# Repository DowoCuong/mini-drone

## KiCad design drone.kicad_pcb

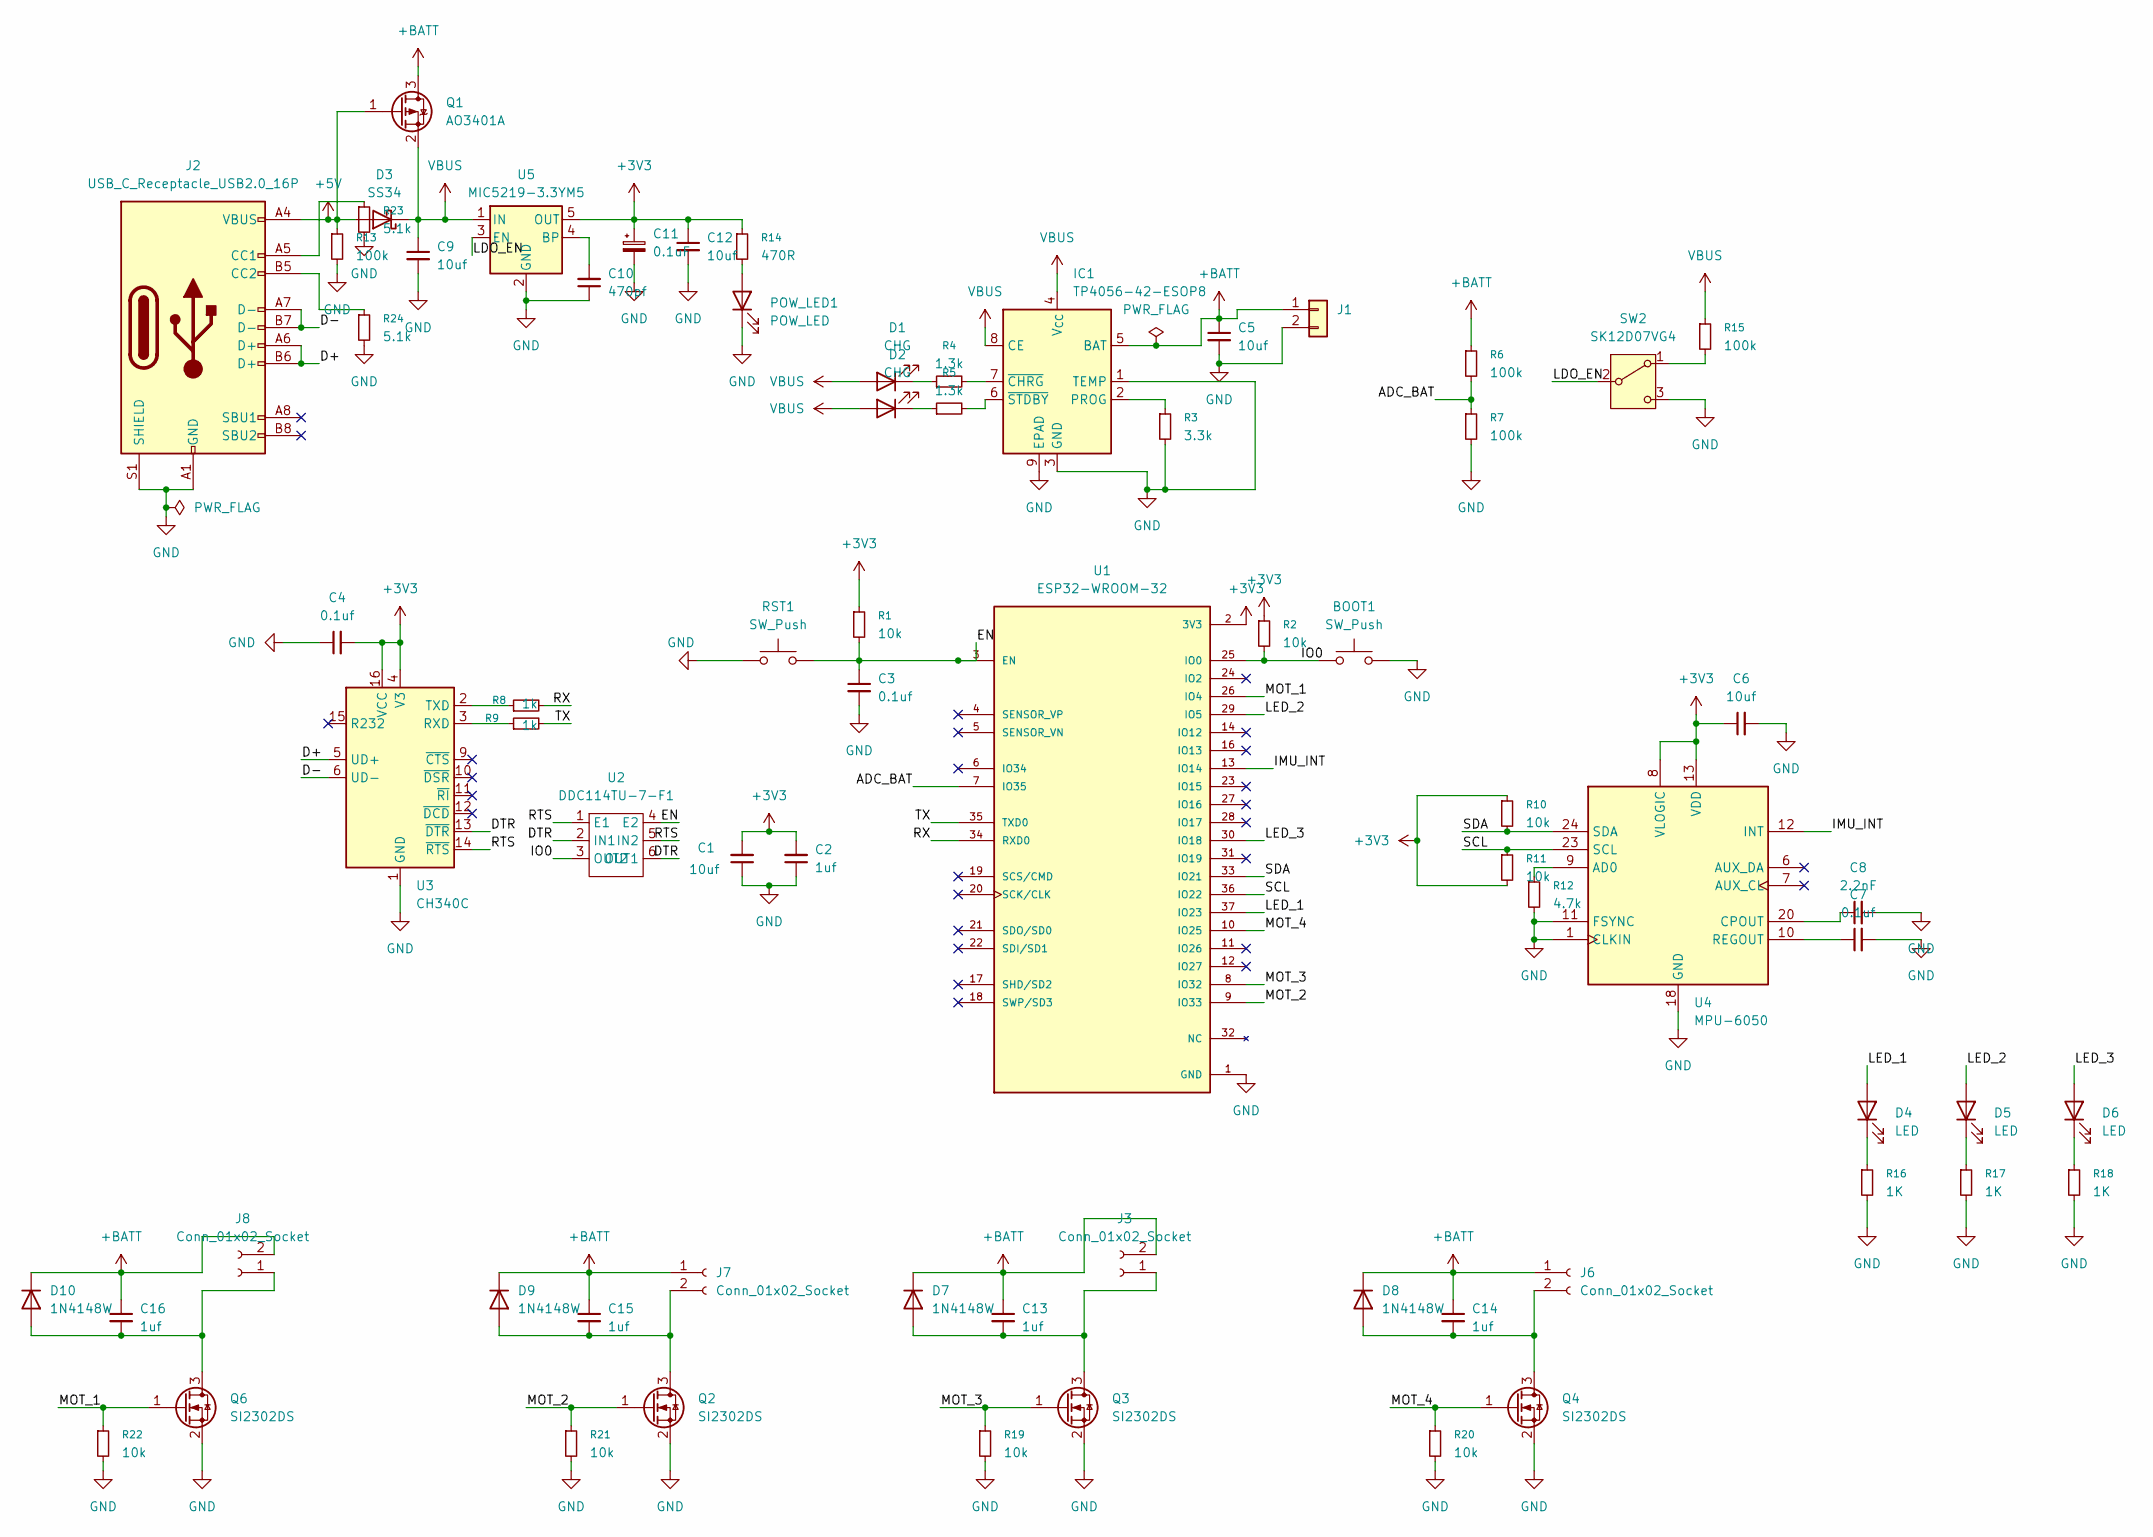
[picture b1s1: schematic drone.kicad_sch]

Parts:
BOOT1: SW_Push; SW_SPST_TL3342
C1, C5, C6, C9, C12: 10uf; C_0603_1608Metric
C2, C13, C14, C15, C16: 1uf; C_0603_1608Metric
C3, C4, C7: 0.1uf; C_0603_1608Metric
C8: 2.2nF; C_0603_1608Metric
C10: 470pf; C_0603_1608Metric
C11: 0.1uF; C_0805_2012Metric
D1, D2: CHG; LED_0603_1608Metric
D3: SS34; D_SMA
D4, D5, D6: LED; LED_0603_1608Metric
D7, D8, D9, D10: 1N4148W; D_SOD-123F
IC1: TP4056-42-ESOP8; SOIC-8-1EP_3.9x4.9mm_P1.27mm_EP2.41x3.3mm_ThermalVias
J1: SolderPads_2x_0.75sqmm_P4.8mm
J2: USB_C_Receptacle_USB2.0_16P; USB_C_HRO_TYPE-C-31-M-12_Drone
J3, J6, J7, J8: Conn_01x02_Socket; SolderPads_2x_0.75sqmm_P4.8mm
POW_LED1: POW_LED; LED_0603_1608Metric
Q1: AO3401A; SOT-23
Q2, Q3, Q4, Q6: SI2302DS; SOT-23
R1, R2, R10, R11, R19, R20, R21, R22: 10k; R_0603_1608Metric
R3: 3.3k; R_0603_1608Metric
R4, R5: 1.3k; R_0603_1608Metric
R6, R7, R13, R15: 100k; R_0603_1608Metric
R8, R9: 1k; R_0603_1608Metric
R12: 4.7k; R_0603_1608Metric
R14: 470R; R_0603_1608Metric
R16, R17, R18: 1K; R_0603_1608Metric
R23, R24: 5.1k; R_0603_1608Metric
RST1: SW_Push; SW_SPST_TL3342
SW2: SK12D07VG4; SW_SPDT_SK12D07VG4_THT
U1: ESP32-WROOM-32; MODULE_ESP32-WROOM-32_Drone_AntennaKeepout; PARTREV 2.9
U2: DDC114TU-7-F1; SOT-363_SC-70-6
U3: CH340C; SOIC-16_3.9x9.9mm_P1.27mm
U4: MPU-6050; InvenSense_QFN-24_4x4mm_P0.5mm
U5: MIC5219-3.3YM5; SOT-23-5

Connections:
+3V3: C1.2, C2.2, C4.2, C6.1, C11.1, C12.1, R1.1, R2.1, R10.1, R11.2, R14.1, U1.2 (3V3), U3.4 (V3), U3.16 (VCC), U4.8 (VLOGIC), U4.13 (VDD), U5.5 (OUT)
+5V: D3.2 (A), J2.A4 (VBUS), J2.A9 (VBUS), J2.B4 (VBUS), J2.B9 (VBUS), Q1.1 (G), R13.1
+BATT: C5.1, C13.1, C14.1, C15.1, C16.1, D7.1 (K), D8.1 (K), D9.1 (K), D10.1 (K), IC1.5 (BAT), J1.1, J3.2, J6.1, J7.1, J8.2, Q1.3 (D), R6.1
/ADC_BAT: R6.2, R7.1, U1.7 (IO35)
/D+: J2.A6 (D+), J2.B6 (D+), U3.5 (UD+)
/D-: J2.A7 (D-), J2.B7 (D-), U3.6 (UD-)
/DTR: U2.2 (IN1), U2.6 (OUT1), U3.13 (~DTR)
/EN: C3.1, R1.2, RST1.2, U1.3 (EN), U2.4 (E2)
/IMU_INT: U1.13 (IO14), U4.12 (INT)
/IO0: BOOT1.1, R2.2, U1.25 (IO0), U2.3 (OUT2)
/LDO_EN: SW2.2 (B), U5.3 (EN)
/LED_1: D4.2 (A), U1.37 (IO23)
/LED_2: D5.2 (A), U1.29 (IO5)
/LED_3: D6.2 (A), U1.30 (IO18)
/MOT_1: Q6.1 (G), R22.1, U1.26 (IO4)
/MOT_2: Q2.1 (G), R21.1, U1.9 (IO33)
/MOT_3: Q3.1 (G), R19.1, U1.8 (IO32)
/MOT_4: Q4.1 (G), R20.1, U1.10 (IO25)
/RTS: U2.1 (E1), U2.5 (IN2), U3.14 (~RTS)
/RX: R8.2, U1.34 (RXD0)
/SCL: R11.1, U1.36 (IO22), U4.23 (SCL)
/SDA: R10.2, U1.33 (IO21), U4.24 (SDA)
/TX: R9.2, U1.35 (TXD0)
GND: BOOT1.2, C1.1, C2.1, C3.2, C4.1, C5.2, C6.2, C7.2, C8.2, C9.2, C10.1, C11.2, C12.2, IC1.1 (TEMP), IC1.3 (GND), IC1.9 (EPAD), J1.2, J2.A1 (GND), J2.A12 (GND), J2.B1 (GND), J2.B12 (GND), J2.S1 (SHIELD), POW_LED1.1 (K), Q2.2 (S), Q3.2 (S), Q4.2 (S), Q6.2 (S), R3.2, R7.2, R12.2, R13.2, R16.2, R17.2, R18.2, R19.2, R20.2, R21.2, R22.2, R23.2, R24.2, RST1.1, SW2.3 (C), U1.1 (GND), U1.15 (GND), U1.38 (GND), U1.39_1 (GND), U1.39_2 (GND), U1.39_3 (GND), U1.39_4 (GND), U1.39_5 (GND), U1.39_6 (GND), U1.39_7 (GND), U1.39_8 (GND), U1.39_9 (GND), U1.39_10 (GND), U1.39_11 (GND), U1.39_12 (GND), U1.39_13 (GND), U1.39_14 (GND), U1.39_15 (GND), U1.39_16 (GND), U1.39_17 (GND), U1.39_18 (GND), U1.39_19 (GND), U1.39_20 (GND), U1.39_21 (GND), U3.1 (GND), U4.1 (CLKIN), U4.11 (FSYNC), U4.18 (GND), U5.2 (GND)
unnamed: D1.1 (K), R4.1
unnamed: D2.1 (K), R5.1
unnamed: D4.1 (K), R16.1
unnamed: D5.1 (K), R17.1
unnamed: D6.1 (K), R18.1
unnamed: C13.2, D7.2 (A), J3.1, Q3.3 (D)
unnamed: C14.2, D8.2 (A), J6.2, Q4.3 (D)
unnamed: C15.2, D9.2 (A), J7.2, Q2.3 (D)
unnamed: C16.2, D10.2 (A), J8.1, Q6.3 (D)
unnamed: IC1.2 (PROG), R3.1
unnamed: IC1.7 (~CHRG), R4.2
unnamed: IC1.6 (~STDBY), R5.2
unnamed: J2.A5 (CC1), R23.1
unnamed: J2.B5 (CC2), R24.1
unnamed: POW_LED1.2 (A), R14.2
unnamed: R15.2, SW2.1 (A)
unnamed: R9.1, U3.3 (RXD)
unnamed: R8.1, U3.2 (TXD)
unnamed: R12.1, U4.9 (AD0)
unnamed: C8.1, U4.20 (CPOUT)
unnamed: C7.1, U4.10 (REGOUT)
unnamed: C10.2, U5.4 (BP)
VBUS: C9.1, D1.2 (A), D2.2 (A), D3.1 (K), IC1.4 (V_{CC}), IC1.8 (CE), Q1.2 (S), R15.1, U5.1 (IN)

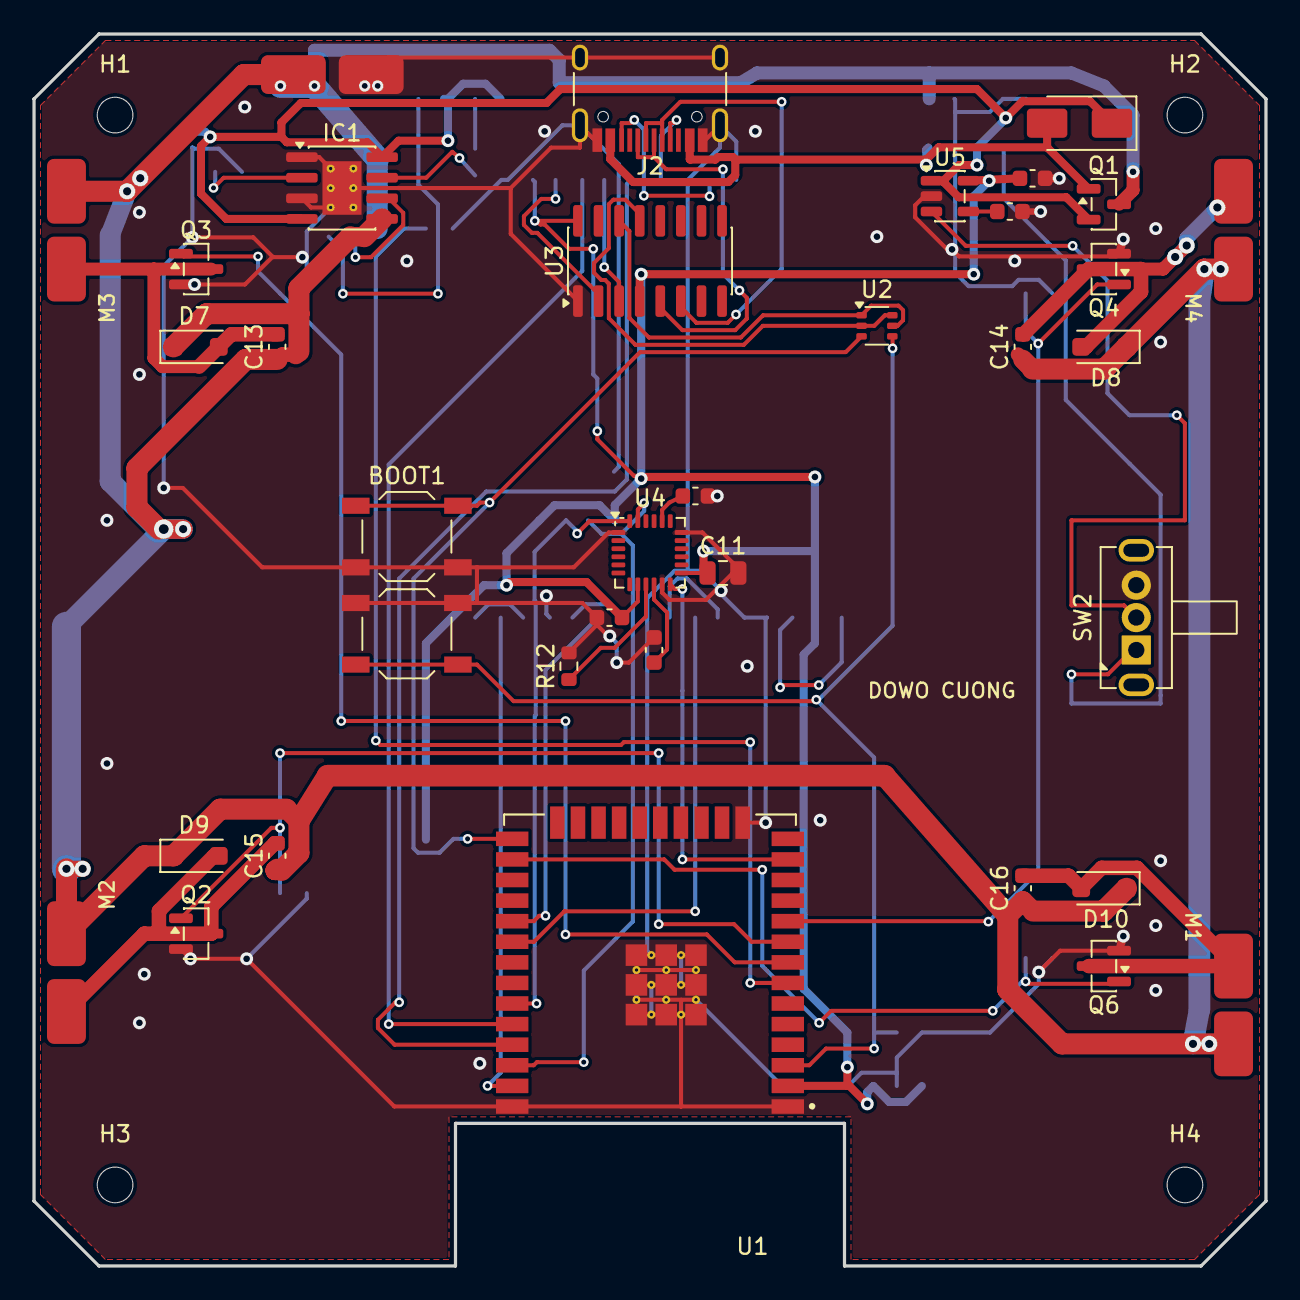
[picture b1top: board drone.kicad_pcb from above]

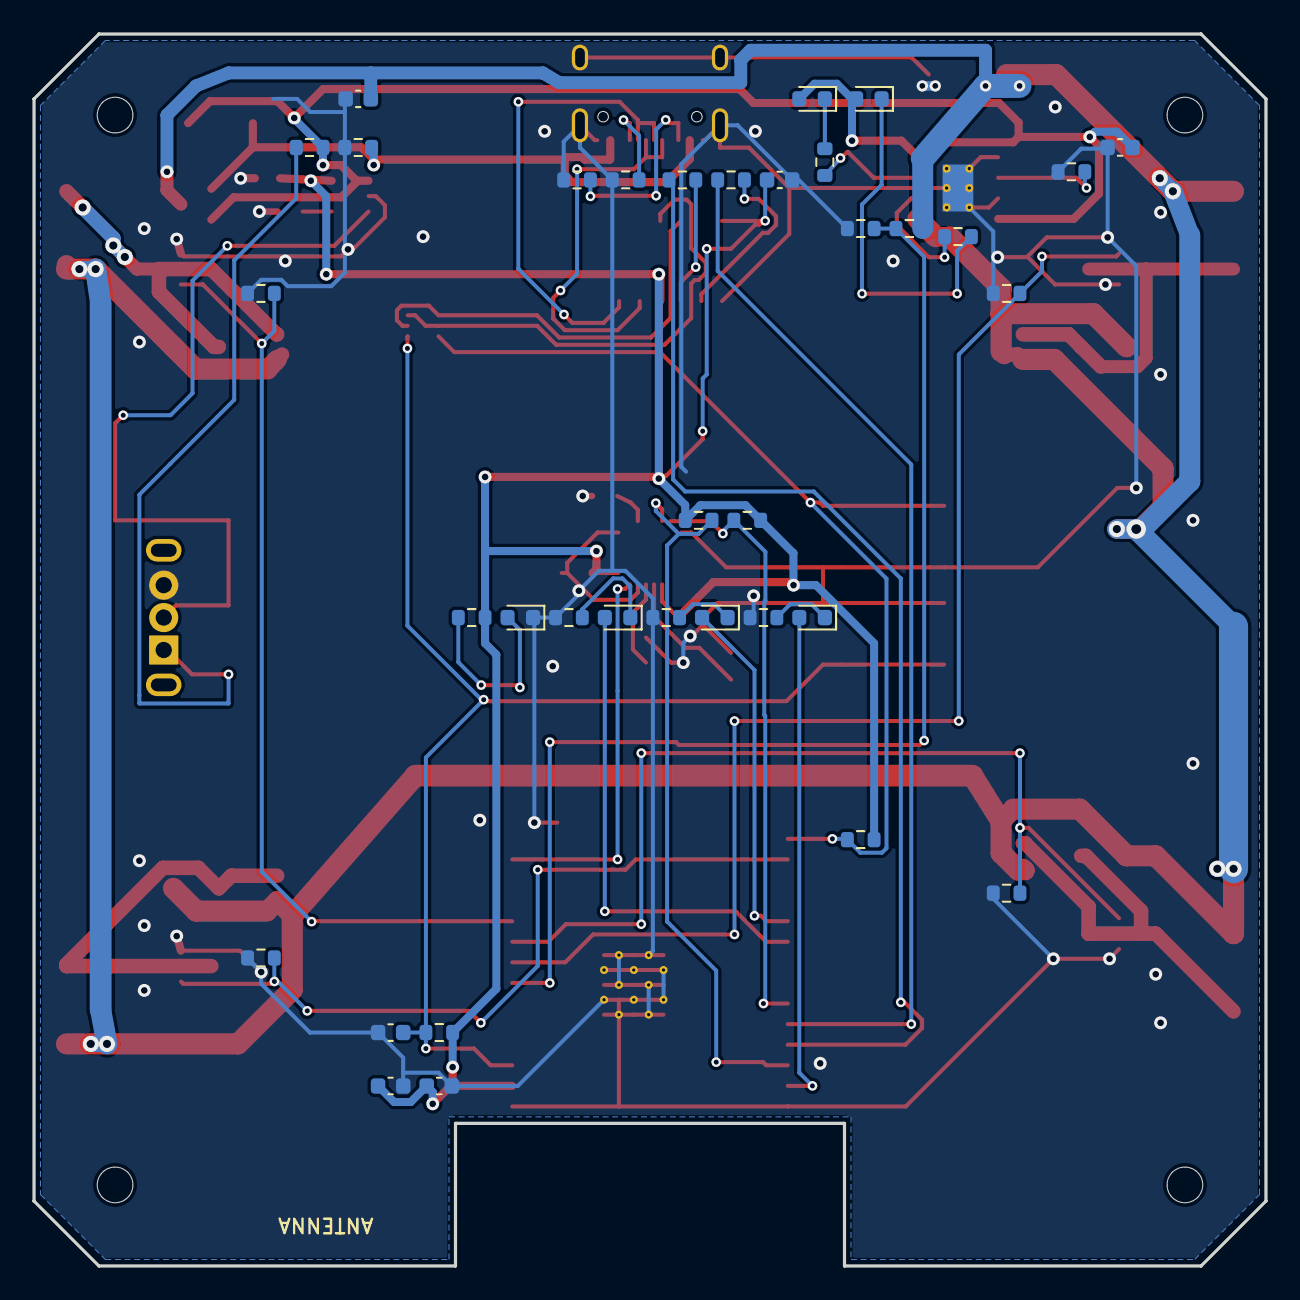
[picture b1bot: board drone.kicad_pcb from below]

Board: 2 copper layers, 76.0 x 76.0 mm, 75 parts (35 on the bottom side), 47 nets.

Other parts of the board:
H1, H2, H3, H4: MountingHole_2.2mm_M2
